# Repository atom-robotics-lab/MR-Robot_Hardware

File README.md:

<!-- Improved compatibility of back to top link: See: https://github.com/othneildrew/Best-README-Template/pull/73 -->

<!--
*** Thanks for checking out the Best-README-Template. If you have a suggestion
*** that would make this better, please fork the repo and create a pull request
*** or simply open an issue with the tag "enhancement".
*** Don't forget to give the project a star!
*** Thanks again! Now go create something AMAZING! :D
-->

<!-- PROJECT SHIELDS -->
<!--
*** I'm using markdown "reference style" links for readability.
*** Reference links are enclosed in brackets [ ] instead of parentheses ( ).
*** See the bottom of this document for the declaration of the reference variables
*** for contributors-url, forks-url, etc. This is an optional, concise syntax you may use.
*** https://www.markdownguide.org/basic-syntax/#reference-style-links
-->
[![Contributors][contributors-shield]][contributors-url]
[![Forks][forks-shield]][forks-url]
[![Stargazers][stars-shield]][stars-url]
[![Issues][issues-shield]][issues-url]
[![LinkedIn][linkedin-shield]][linkedin-url]

<!-- PROJECT LOGO -->
<br />
<div align="center">

<h3 align="center">MR Robot</h3>

  <p align="center">
    This is the repo for the <a href="https://github.com/atom-robotics-lab/MR-Robot">MR-Robot: ModulaR Robot</a> Project, Mr robot is autonomous navigation robot made by A.T.O.M Robotics capable of doing multiple day to day operations such as mapping, navigation for transportation, sanitaion etc. Various other operations can also be performed thanks to its modularity.
    If you’re interested in helping to improve our Project</a>, find out how to <a href="https://github.com/atom-robotics-lab/MR-Robot/blob/main/contributing.md">contribute<a>. 
    <br />
    <a href=""><strong>Demo video »</strong></a>
    <br />
    <br />
    <a href="https://github.com/atom-robotics-lab/MR-Robot/issues/new?labels=bug&assignees=jasmeet0915,Kartik9250,insaaniManav,namikxgithub">Report Bug</a>
    ·
    <a href="https://github.com/atom-robotics-lab/MR-Robot/issues/new?labels=enhancement&assignees=jasmeet0915,Kartik9250,insaaniManav,namikxgithub">Request Feature</a>
  </p>
</div>

<!-- ABOUT THE PROJECT -->
## About The Project

This is the repo for the <a href="https://github.com/atom-robotics-lab/MR-Robot">MR-Robot: ModulaR Robot</a> Project, Mr robot is autonomous navigation robot made by A.T.O.M Robotics capable of doing multiple day to day operations such as mapping, navigation for transportation, sanitaion etc. Various other operations can also be performed thanks to its modularity.
If you’re interested in helping to improve our Project</a>, find out how to <a href="https://github.com/atom-robotics-lab/MR-Robot/contributing.md">contribute<a>.   

<p align="right">(<a href="#readme-top">back to top</a>)</p>

### Built With

* 
* 
* 
* 
* 
* 
* 

<p align="right">(<a href="#readme-top">back to top</a>)</p>

# DFD

# MR-Robot Circuit Diagram

# CONNECTION BETWEEN COMPUTER AND PI 
Now we have to setup a connection between the PC (Master) and the Pi(slave) for that we need to host the ip of the PC and get the Pi to connect to it.
For this get inside of the bashrc of the PC using command.
```shell
gedit .bashrc
```
And add the following lines
```shell
export ROS_MASTER_URI=http://localhost:11311/
export ROS_HOSTNAME=IP Address of PC
export ROS_IP= IP Address of PC
```
Now navigate into the pi and use the command
```shell
export ROS_MASTER_URI=http://IP Address of PC:11311/
export ROS_HOSTNAME=IP Address of PI
export ROS_IP=IP Address of PI
```
# ASSIGNING PORT FOR LIDAR AND ESP

It is crucial to assign ports for LIDAR and ESP because both of them receive random ports in ttyUSB format. 

Use This command to identify port and characters after "usb"

```shell
dmesg | grep ttyUSB
```

For creating the link from USB ports to the devices:-

```shell
sudo nano /etc/udev/rules.d/10-usb-serial.rules
```

```shell
SUBSYSTEM=="tty", KERNELS=="1-1.4", SYMLINK+="ttyUSB_ESP"
SUBSYSTEM=="tty", KERNELS=="1-1.1", SYMLINK+="ttyUSB_LIDAR"
```

For loading the new rules:-

```shell
sudo udevadm trigger
```

By running the next command in the Terminal, you may verify the new names you just made:-

```shell
ls -l /dev/ttyUSB*
```

# LAUNCHING LIDAR

```shell
roslaunch ydlidar_ros X2L.launch
```

This command will start ***"/scan"*** topic which will provide lidar data to pi which ultimately reaches Navigation Stack.

# ESP32 USAGE

ESP32 is controlling all the moter realted task in the bot it is receiving value of PWM from topic ***"/left_pwm"*** and ***"/right_pwm"*** which is then given to motor driver.

ESP32 receiving feedback data form motor's encoder by subscribing to the topic ***"/left_encoder"*** and ***"/right_encoder"*** which is then used in calculation odometry by pi.

# Launching Odom Calculation Node

```shell
rosrun mr_robot_firmware diff_tf.py
```

This node calculates odom from left encoder data and right encoder data.

# Launching Twist To PWM Node

```shell
rosrun mr_robot_firmware twist_to_pwm.py
```

This node converts Twist data into a signal using PWM for ESP32.
<!-- CONTACTS -->
## Contacts

Our Socials - [Linktree](https://linktr.ee/atomlabs) - atom@inventati.org

<p align="right">(<a href="#readme-top">back to top</a>)</p>

<!-- ACKNOWLEDGMENTS-->
## Acknowledgement

* [Our wiki](https://atom-robotics-lab.github.io/wiki)
* [ROS Official Documentation](http://wiki.ros.org/Documentation)
* [Opencv Official Documentation](https://docs.opencv.org/4.x/)
* [Rviz Documentation](http://wiki.ros.org/rviz)
* [Gazebo Tutorials](https://classic.gazebosim.org/tutorials)
* [Ubuntu Installation guide](https://ubuntu.com/tutorials/install-ubuntu-desktop#1-overview)
* [Raspberrypi Documentation](https://www.raspberrypi.com/documentation/)
* [Esp32 Documentation](https://docs.espressif.com/projects/esp-idf/en/latest/esp32/)
* [Blender Documentaion](https://docs.blender.org/)

<p align="right">(<a href="#readme-top">back to top</a>)</p>

<!-- MARKDOWN LINKS & IMAGES -->
<!-- https://www.markdownguide.org/basic-syntax/#reference-style-links -->
[contributors-shield]: https://img.shields.io/github/contributors/atom-robotics-lab/MR-Robot_Hardware.svg?style=for-the-badge
[contributors-url]: https://github.com/atom-robotics-lab/MR-Robot_Hardware/graphs/contributors
[forks-shield]: https://img.shields.io/github/forks/atom-robotics-lab/MR-Robot_Hardware.svg?style=for-the-badge
[forks-url]: https://github.com/atom-robotics-lab/MR-Robot_Hardware/network/members
[stars-shield]: https://img.shields.io/github/stars/atom-robotics-lab/MR-Robot_Hardware.svg?style=for-the-badge
[stars-url]: https://github.com/atom-robotics-lab/MR-Robot_Hardware/stargazers
[issues-shield]: https://img.shields.io/github/issues/atom-robotics-lab/MR-Robot_Hardware.svg?style=for-the-badge
[issues-url]: https://github.com/atom-robotics-lab/MR-Robot_Hardware/issues
[linkedin-shield]: https://img.shields.io/badge/-LinkedIn-black.svg?style=for-the-badge&logo=linkedin&colorB=555
[linkedin-url]: https://www.linkedin.com/company/a-t-o-m-robotics-lab/

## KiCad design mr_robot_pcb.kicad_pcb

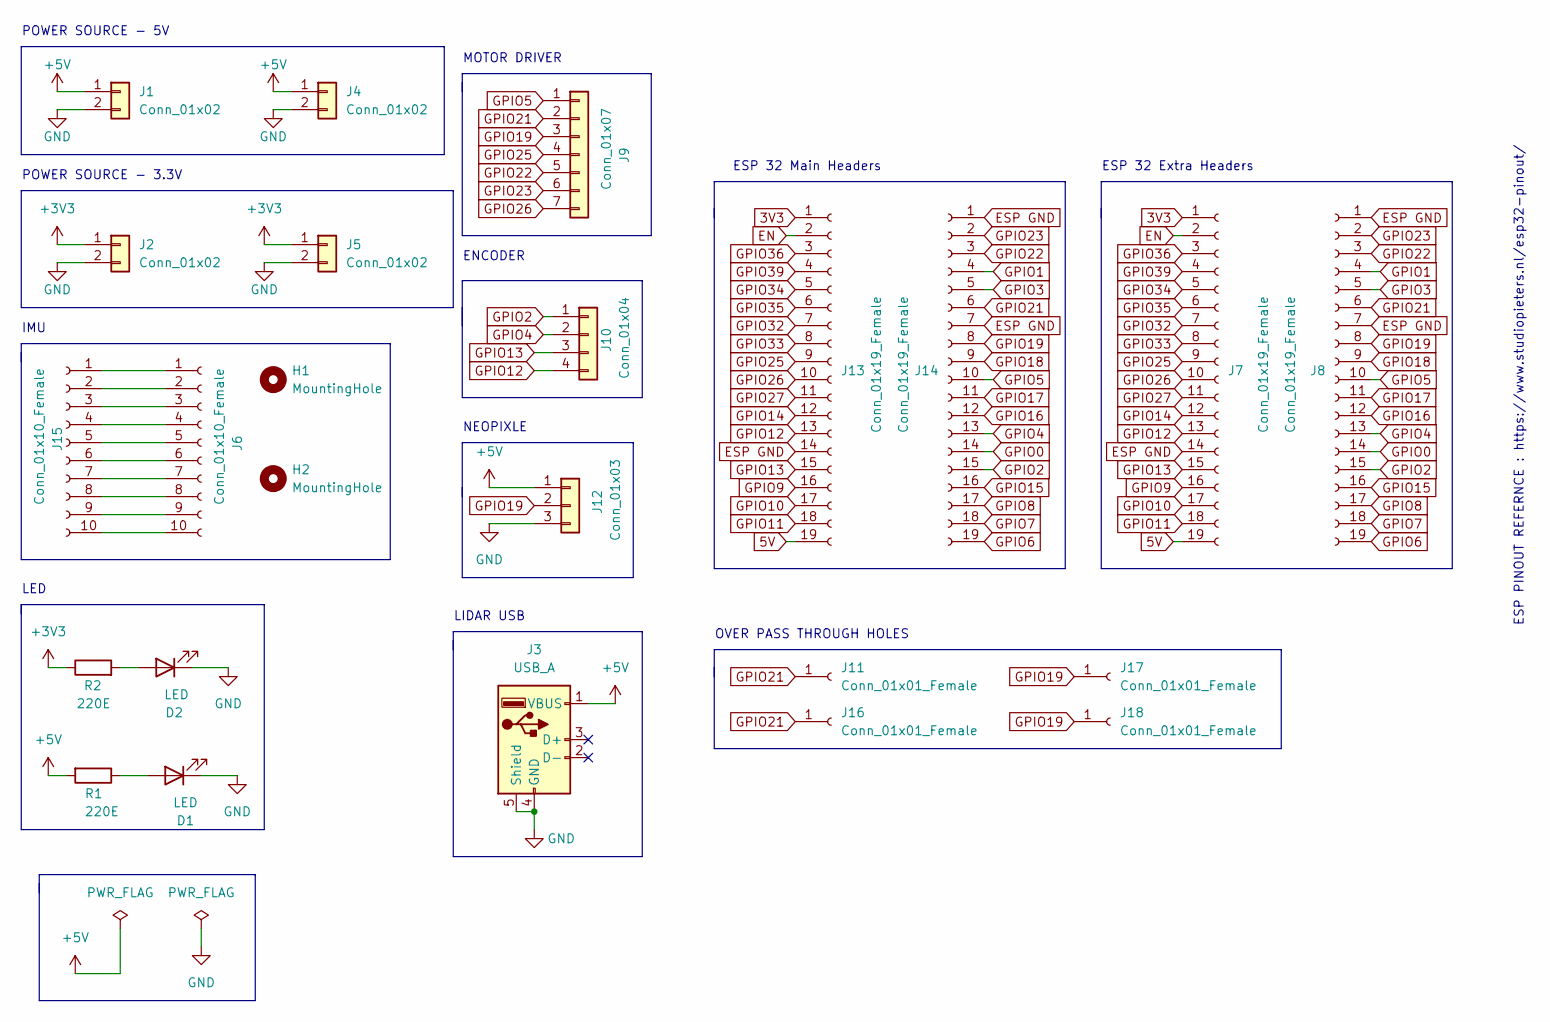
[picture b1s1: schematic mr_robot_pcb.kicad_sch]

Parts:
D1, D2: LED; LED_D5.0mm
H1, H2: MountingHole; MountingHole_2.1mm
J1, J2, J4, J5: Conn_01x02; JST_EH_B2B-EH-A_1x02_P2.50mm_Vertical
J3: USB_A; USB_A_Molex_67643_Horizontal
J6, J15: Conn_01x10_Female; PinHeader_1x10_P2.54mm_Vertical
J7, J8, J13, J14: Conn_01x19_Female; PinHeader_1x19_P2.54mm_Vertical
J9: Conn_01x07; JST_EH_B7B-EH-A_1x07_P2.50mm_Vertical
J10: Conn_01x04; JST_EH_B4B-EH-A_1x04_P2.50mm_Vertical
J11, J16, J17, J18: Conn_01x01_Female; PinSocket_1x01_P2.54mm_Vertical
J12: Conn_01x03; JST_EH_B3B-EH-A_1x03_P2.50mm_Vertical
R1, R2: 220E; R_Axial_DIN0204_L3.6mm_D1.6mm_P5.08mm_Horizontal

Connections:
3V3: J7.1, J13.1
5V: J7.19, J13.19
+3V3: J2.1, J5.1, R2.1
+5V: J1.1, J3.1 (VBUS), J4.1, J12.1, R1.2
EN: J7.2, J13.2
ESP GND: J7.14, J8.1, J8.7, J13.14, J14.1, J14.7
GND: D1.1 (K), D2.1 (K), J1.2, J2.2, J3.4 (GND), J3.5 (Shield), J4.2, J5.2, J12.3
GPIO0: J8.14, J14.14
GPIO1: J8.4, J14.4
GPIO2: J8.15, J10.1, J14.15
GPIO3: J8.5, J14.5
GPIO4: J8.13, J10.2, J14.13
GPIO5: J8.10, J9.1, J14.10
GPIO6: J8.19, J14.19
GPIO7: J8.18, J14.18
GPIO8: J8.17, J14.17
GPIO9: J7.16, J13.16
GPIO10: J7.17, J13.17
GPIO11: J7.18, J13.18
GPIO12: J7.13, J10.4, J13.13
GPIO13: J7.15, J10.3, J13.15
GPIO14: J7.12, J13.12
GPIO15: J8.16, J14.16
GPIO16: J8.12, J14.12
GPIO17: J8.11, J14.11
GPIO18: J8.9, J14.9
GPIO19: J8.8, J9.3, J12.2, J14.8, J17.1, J18.1
GPIO21: J8.6, J9.2, J11.1, J14.6, J16.1
GPIO22: J8.3, J9.5, J14.3
GPIO23: J8.2, J9.6, J14.2
GPIO25: J7.9, J9.4, J13.9
GPIO26: J7.10, J9.7, J13.10
GPIO27: J7.11, J13.11
GPIO32: J7.7, J13.7
GPIO33: J7.8, J13.8
GPIO34: J7.5, J13.5
GPIO35: J7.6, J13.6
GPIO36: J7.3, J13.3
GPIO39: J7.4, J13.4
unnamed: D1.2 (A), R1.1
unnamed: D2.2 (A), R2.2
unnamed: J6.1, J15.1
unnamed: J6.2, J15.2
unnamed: J6.3, J15.3
unnamed: J6.4, J15.4
unnamed: J6.5, J15.5
unnamed: J6.6, J15.6
unnamed: J6.7, J15.7
unnamed: J6.8, J15.8
unnamed: J6.9, J15.9
unnamed: J6.10, J15.10

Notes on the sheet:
ESP PINOUT REFERNCE : https://www.studiopieters.nl/esp32-pinout/
ESP 32 Extra Headers
POWER SOURCE - 3.3V
MOTOR DRIVER
POWER SOURCE - 5V
LED
OVER PASS THROUGH HOLES
LIDAR USB
IMU
ENCODER
NEOPIXLE
ESP 32 Main Headers

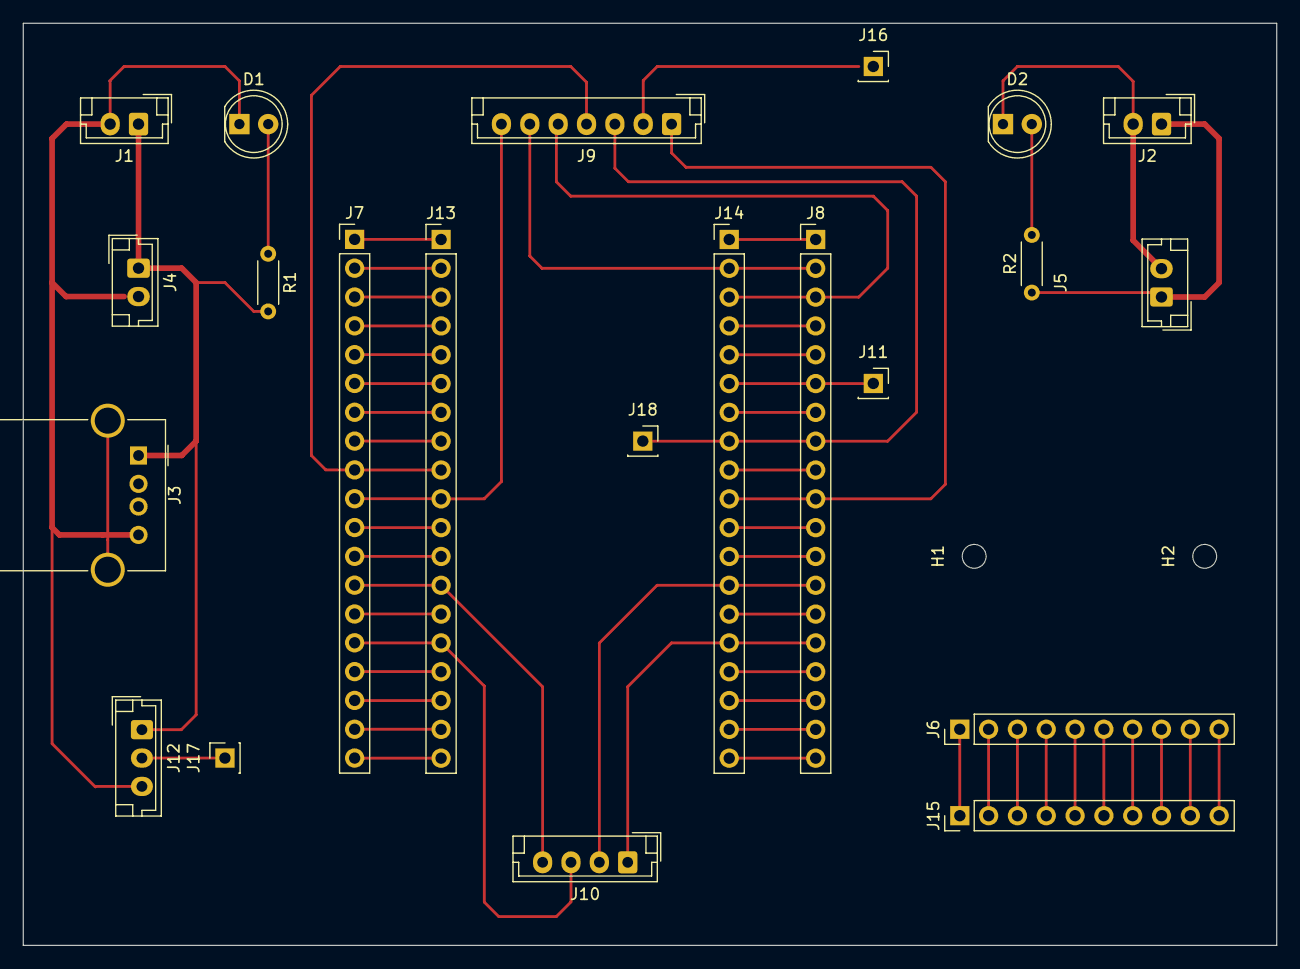
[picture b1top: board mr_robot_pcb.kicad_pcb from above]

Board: 2 copper layers, 110.5 x 81.3 mm, 24 parts (0 on the bottom side), 51 nets.

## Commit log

2022-04-24 added new firmware package and ydlidar_ros submudule
2022-04-24 added scripts for camera and moter_control
2022-04-26 Added script for differential drive
2022-04-26 fixed the wheel velocity
2022-04-30 testing for gpio
2022-04-30 gpio fix
2022-05-09 added launch file
2022-05-09 finished diff.py script
2022-05-09 added print statememnt
2022-05-09 changed params
2022-05-09 fixed pwm_speed
2022-05-09 fixed issue
2022-05-09 fixed stop function
2022-05-12 added camera node
2022-05-12 added launch file to start robot
2022-05-12 flipped image output
2022-05-12 fixed flip
2022-05-12 added flipped frame
2022-05-12 fixed flipped frame
2022-05-12 fixed launch file
2022-05-25 OOPS programming + rosparams
2022-05-26 added try - except - finally block
2022-05-26 added cmdvel publisher
2022-05-26 encoder_odom corrected
2022-05-26 encoder_odom.py corrected
2022-05-31 changes made after comments
2022-05-31 changed rosparam variables
2022-06-02 fixed variable names
2022-06-02 new function for change of duty cycle
2022-09-30 remmoved sub module
2022-09-30 remvoed submodule
2022-09-30 added yd_lidar
2022-10-13 joy add
2022-10-13 odom script updated
2022-10-14 added odom_pub
2022-10-14 fixed file directory
2022-10-17 Updated launch file
2022-12-08 fix1.md
2022-12-08 fix2
2022-12-08 fix3
2022-12-08 fix4.md
2022-12-08 fix5.md
2022-12-08 fix6.md
2022-12-08 added assets
2022-12-08 fixed wire thick
2022-12-08 added dfd and diagram
2022-12-08 gen_fix
2022-12-09 circuit fix
2022-12-09 changed pin
2022-12-09 removed odom pub from catkin_make list
2022-12-14 added param
2022-12-14 added in launch
2022-12-15 added sh file
2022-12-15 rename file
2022-12-16 change port
2022-12-16 pwm value change
2022-12-16 launch file port fix
2022-12-16 added base_link in X2l
2022-12-16 tf fixed
2022-12-16 changed to lidar_1
2022-12-16 Added portpics
2022-12-16 added usbport link
2022-12-17 one machine Launch
2022-12-17 twist class
2022-12-17 joy twist class
2022-12-18 added pwm joy class
2022-12-19 50 main joy
2022-12-21 cpp file working
2022-12-28 added imu drivers
2022-12-28 removed unnecessary file
2022-12-28 ip change
2022-12-29 added robot_pose_ekf
2023-01-01 removed comment
2023-01-03 launch
2023-01-14 added update_pose to the diff_tf.py
2023-01-18 added publisher and subscriber for the velocity
2023-01-18 fixed minor issues
2023-01-18 added p correction for the pwm value
2023-01-21 fixed minor issue
2023-01-21 actual speed
2023-01-21 added P
2023-03-05 Update README.md
    remove blender logo
2023-03-05 Update README.md
    fix no image issue
2023-03-23 new config
2023-03-23 Added joy_to_twist
2023-03-23 completed joy_to_twist
2023-03-23 added manouver launch file
2023-03-24 added arm control
2023-03-24 fixed joy_to_twist
2023-05-07 Added PCB file for MR_Robot
2023-09-27 merged sp + mr
2023-10-14 ip chnage
2023-10-14 left right encoder
2023-10-15 map added with fix
2023-10-15 fixed controller script
2023-10-15 fixed led intigration
2023-10-20 update ip
2023-11-22 Add led code in encoder.ino
2023-12-16 encoder
2024-08-13 removed python package
2024-08-13 Added Dockerfile
2024-08-14 Master env variable
2024-08-18 Added build bashscript
2024-08-20 Changed deprecated ledcsetup and ledcattachpin fn with ledcattach fn
2024-08-23 Added ros commands
2024-08-30 changed some configuration and added some dependency in dockerfile
